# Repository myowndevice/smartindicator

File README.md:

## Умный индикатор

Вы можете самостоятельно сделать индикатор любой формы из данного набора деталей. Данный радиоконструктор базируется на микроконтроллере STM8 и позволит вам приобрести навыки программирования микроконтроллеров. Он позволяет построить умный индикатор, имеющий следующие характеристики:

- Компактный размер — минимум 20х20 мм
- Толщина всего 2 мм
- Управление по одному проводу по протоколу 1-wire
- Независимое управление каждым светодиодом
- Управление яркостью — более 100 градаций яркости
- Питание 3-5В
- Потребление тока от 1 до 10 мА, зависит от яркости
- Удобная трассировка платы — один резистор на 20 светодиодов
- До 100 светодиодов в одном индикаторе

Данный репозитарий содержит все необходимые файлы для изготовления индикатора. Если вы будете скачивать файлы через web не забудьте скачать общую папку Kicadlib.

Ознакомится со схемой и подробным описанием индикатора, программы, и порядка сборки можно, [прочитав эту подробную статью](http://myowndevice.ru/index.php/pribory/item/35-umnyj-indikator)

Также [здесь](http://myowndevice.ru) вы найдете подробное описание как сделать другие приборы, много теории о том, как их делать, методику изготовления печатных плат и много другого.

Изучай микроконтроллеры, делай платы дома, разрабатывай электронику сам!

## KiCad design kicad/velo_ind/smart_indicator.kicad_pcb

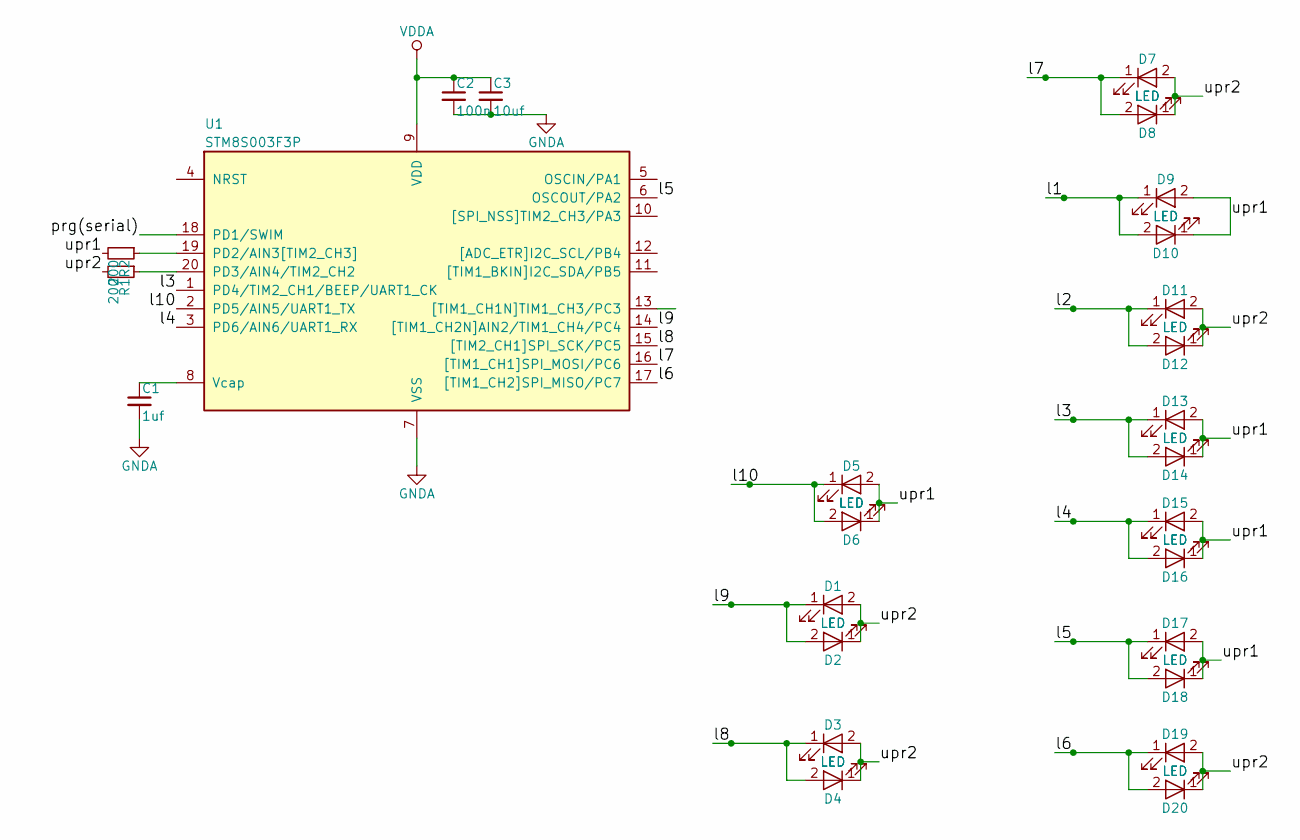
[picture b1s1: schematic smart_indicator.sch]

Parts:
C1: 1uf; C_0805_HandSoldering
C2: 100n; C_0603_HandSoldering
C3: 10uf; C_0805_HandSoldering
D1, D2, D3, D4, D5, D6, D7, D8, D9, D10, D11, D12, D13, D14, D15, D16, D17, D18, D19, D20: LED; LED_0603_HandSoldering
R1, R2: 200; R_0603_HandSoldering
U1: STM8S003F3P; SSOP-20_4.4x6.5mm_Pitch0.65mm

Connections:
/l1: D9.1 (K), D10.2 (A)
/l2: D11.1 (K), D12.2 (A)
/l3: D13.1 (K), D14.2 (A), U1.1 (PD4/TIM2_CH1/BEEP/UART1_CK)
/l4: D15.1 (K), D16.2 (A), U1.3 (PD6/AIN6/UART1_RX)
/l5: D17.1 (K), D18.2 (A), U1.6 (OSCOUT/PA2)
/l6: D19.1 (K), D20.2 (A), U1.17 ([TIM1_CH2]SPI_MISO/PC7)
/l7: D7.1 (K), D8.2 (A), U1.16 ([TIM1_CH1]SPI_MOSI/PC6)
/l8: D3.1 (K), D4.2 (A), U1.15 ([TIM2_CH1]SPI_SCK/PC5)
/l9: D1.1 (K), D2.2 (A), U1.14 ([TIM1_CH2N]AIN2/TIM1_CH4/PC4)
/l10: D5.1 (K), D6.2 (A), U1.2 (PD5/AIN5/UART1_TX)
/prg(serial): U1.18 (PD1/SWIM)
/upr1: D5.2 (A), D6.1 (K), D9.2 (A), D10.1 (K), D13.2 (A), D14.1 (K), D15.2 (A), D16.1 (K), D17.2 (A), D18.1 (K), R2.2
/upr2: D1.2 (A), D2.1 (K), D3.2 (A), D4.1 (K), D7.2 (A), D8.1 (K), D11.2 (A), D12.1 (K), D19.2 (A), D20.1 (K), R1.2
GNDA: C1.2, C2.2, C3.2, U1.7 (VSS)
unnamed: C1.1, U1.8 (Vcap)
unnamed: R1.1, U1.20 (PD3/AIN4/TIM2_CH2)
unnamed: R2.1, U1.19 (PD2/AIN3[TIM2_CH3])
VDDA: C2.1, C3.1, U1.9 (VDD)

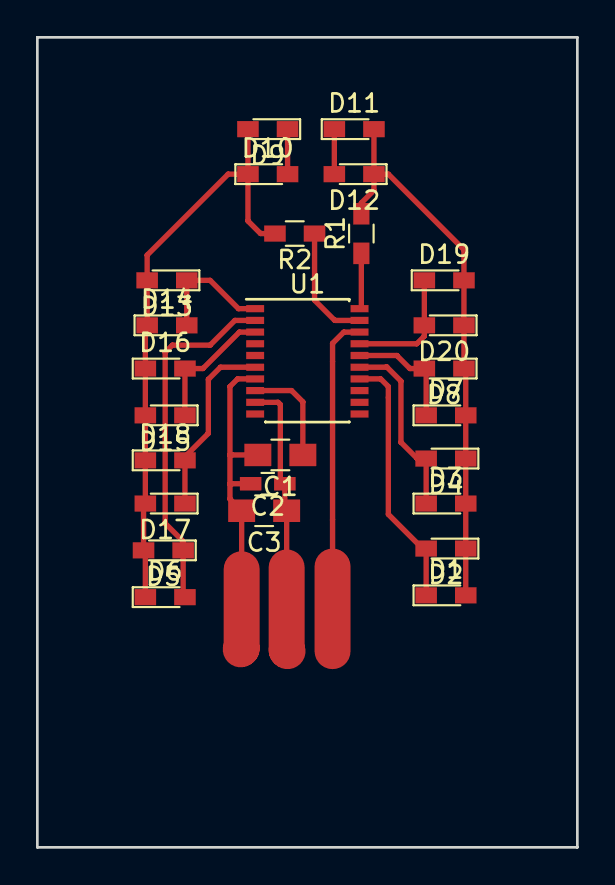
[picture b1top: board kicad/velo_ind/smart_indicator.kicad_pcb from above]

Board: 2 copper layers, 30.0 x 45.0 mm, 26 parts (0 on the bottom side), 17 nets.

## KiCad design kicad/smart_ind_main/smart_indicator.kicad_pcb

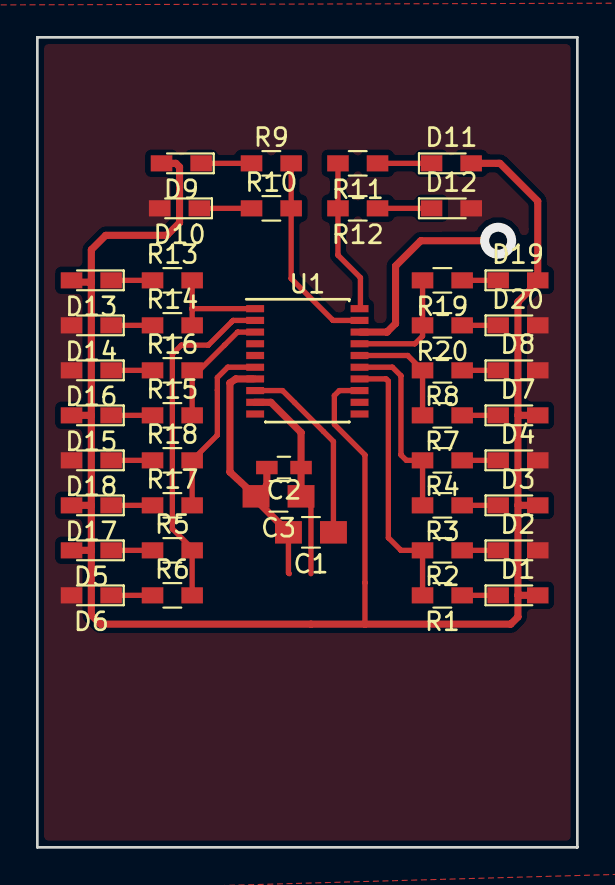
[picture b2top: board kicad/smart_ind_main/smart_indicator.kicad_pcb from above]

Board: 2 copper layers, 30.0 x 45.0 mm, 44 parts (0 on the bottom side), 35 nets.

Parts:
C1: 1uf; C_0805_HandSoldering
C2: 100n; C_0603_HandSoldering
C3: 10uf; C_0805_HandSoldering
D1, D2, D3, D4, D5, D6, D7, D8, D9, D10, D11, D12, D13, D14, D15, D16, D17, D18, D19, D20: LED; LED_0603_HandSoldering
R1, R2, R3, R4, R5, R6, R7, R8, R9, R10, R11, R12, R13, R14, R15, R16, R17, R18, R19, R20: 2k; R_0603_HandSoldering
U1: STM8S003F3P; SSOP-20_4.4x6.5mm_Pitch0.65mm

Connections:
/l1: R9.2, R10.2, U1.19
/l2: R11.2, R12.2, U1.20
/l3: R13.2, R14.2, U1.1
/l4: R15.2, R16.2, U1.3
/l5: R17.2, R18.2, U1.6
/l6: R19.2, R20.2, U1.17
/l7: R7.2, R8.2, U1.16
/l8: R3.2, R4.2, U1.15
/l9: R1.2, R2.2, U1.14
/l10: R5.2, R6.2, U1.2
GND: D2.2, D4.2, D6.2, D8.2, D10.2, D12.2, D14.2, D16.2, D18.2, D20.2, U1.5
GNDA: C1.2, C2.2, C3.2, U1.7
unnamed: C1.1, U1.8
unnamed: D1.1, R1.1
unnamed: D2.1, R2.1
unnamed: D3.1, R3.1
unnamed: D4.1, R4.1
unnamed: D5.1, R5.1
unnamed: D6.1, R6.1
unnamed: D7.1, R7.1
unnamed: D8.1, R8.1
unnamed: D9.1, R9.1
unnamed: D10.1, R10.1
unnamed: D11.1, R11.1
unnamed: D12.1, R12.1
unnamed: D13.1, R13.1
unnamed: D14.1, R14.1
unnamed: D15.1, R15.1
unnamed: D16.1, R16.1
unnamed: D17.1, R17.1
unnamed: D18.1, R18.1
unnamed: D19.1, R19.1
unnamed: D20.1, R20.1
VD: D1.2, D3.2, D5.2, D7.2, D9.2, D11.2, D13.2, D15.2, D17.2, D19.2, U1.13
VDDA: C2.1, C3.1, U1.9

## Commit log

2017-11-28 start
